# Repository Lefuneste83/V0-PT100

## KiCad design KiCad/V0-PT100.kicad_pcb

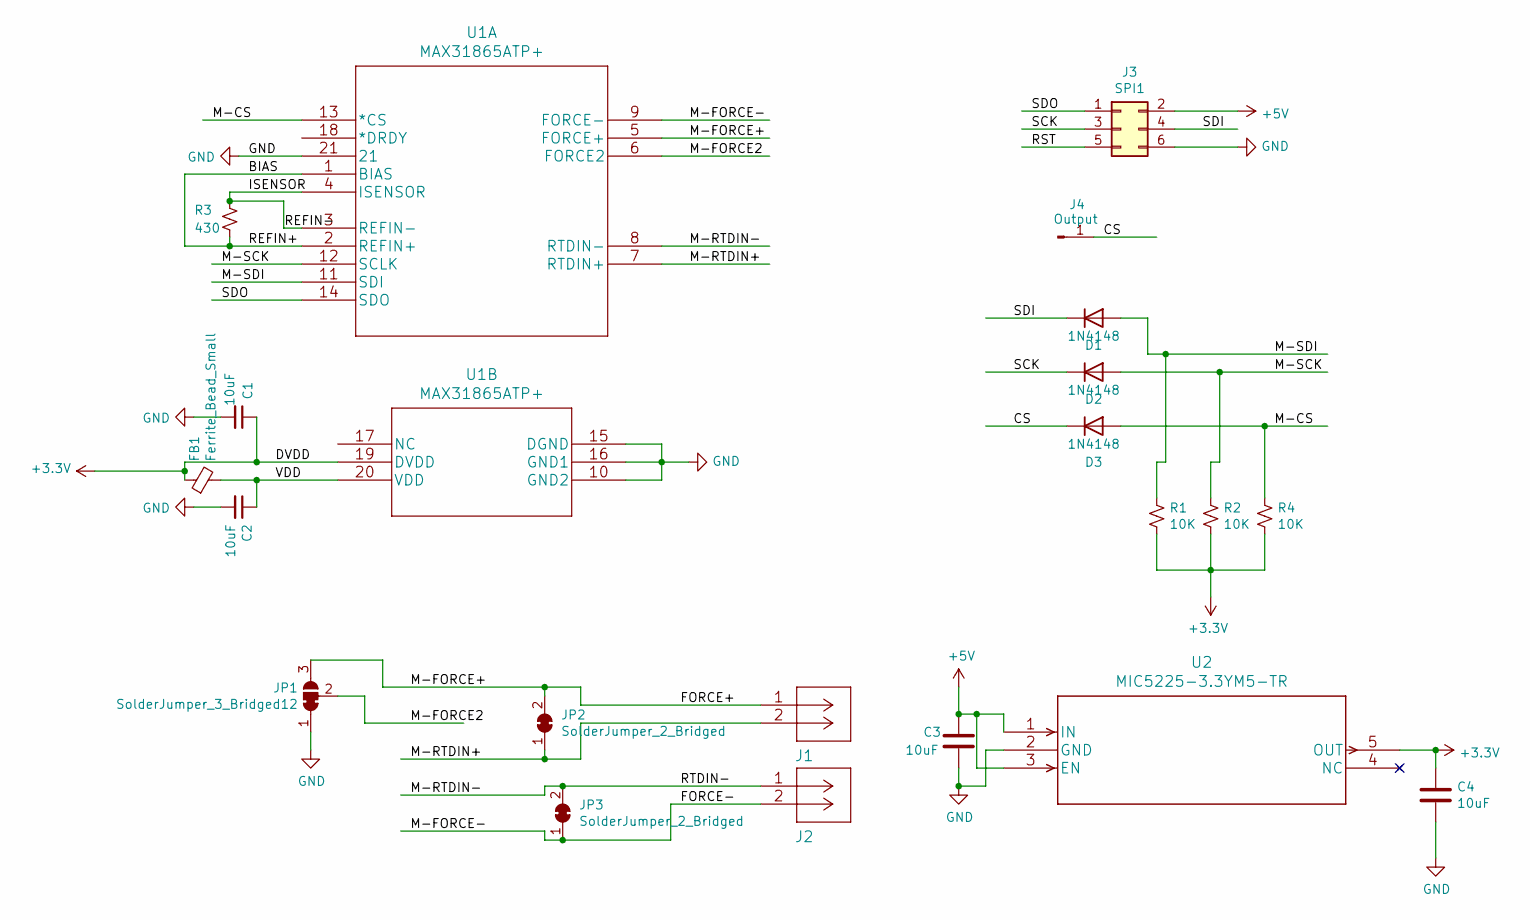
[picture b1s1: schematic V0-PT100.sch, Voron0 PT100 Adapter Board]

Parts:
C1, C2, C3, C4: 10uF; C_0603_1608Metric_Pad1.05x0.95mm_HandSolder
D1, D2, D3: 1N4148; D_SOD-323
FB1: Ferrite_Bead_Small; L_0603_1608Metric_Pad1.05x0.95mm_HandSolder
J1: T1; 1984617
J2: T2; 1984617
J3: SPI1; PinSocket_2x03_P2.54mm_Vertical
J4: Output; PinHeader_1x01_P2.54mm_Horizontal
JP1: SolderJumper_3_Bridged12; SolderJumper-3_P1.3mm_Bridged12_RoundedPad1.0x1.5mm
JP2, JP3: SolderJumper_2_Bridged; SolderJumper-2_P1.3mm_Bridged_RoundedPad1.0x1.5mm
R1, R2, R4: 10K; R_0603_1608Metric_Pad1.05x0.95mm_HandSolder
R3: 430; R_0603_1608Metric_Pad1.05x0.95mm_HandSolder
U1: MAX31865ATP+; MAX31865ATP&plus_
U2: MIC5225-3.3YM5-TR

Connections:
+3V3: C1.1, C4.1, FB1.1, R1.2, R2.2, R4.2, U1.19 (DVDD), U2.5 (OUT)
+5V: C3.1, J3.2, U2.1 (IN), U2.3 (EN)
/BIAS: R3.2, U1.1 (BIAS), U1.2 (REFIN+)
/CS: D3.1 (K), J4.1
/FORCE+: J1.1, JP1.3 (B), JP2.2 (B), U1.5 (FORCE+)
/FORCE-: J2.2, JP3.1 (A), U1.9 (FORCE-)
/ISENSOR: R3.1, U1.3 (REFIN-), U1.4 (ISENSOR)
/M-CS: D3.2 (A), R4.1, U1.13 (*CS)
/M-FORCE2: JP1.2 (C), U1.6 (FORCE2)
/M-RTDIN+: J1.2, JP2.1 (A), U1.7 (RTDIN+)
/M-RTDIN-: J2.1, JP3.2 (B), U1.8 (RTDIN-)
/M-SCK: D2.2 (A), R2.1, U1.12 (SCLK)
/M-SDI: D1.2 (A), R1.1, U1.11 (SDI)
/RST: J3.5
/SCK: D2.1 (K), J3.3
/SDI: D1.1 (K), J3.4
/SDO: J3.1, U1.14 (SDO)
/VDD: C2.1, FB1.2, U1.20 (VDD)
GND: C1.2, C2.2, C3.2, C4.2, J3.6, JP1.1 (A), U1.10 (GND2), U1.15 (DGND), U1.16 (GND1), U1.21, U2.2 (GND)

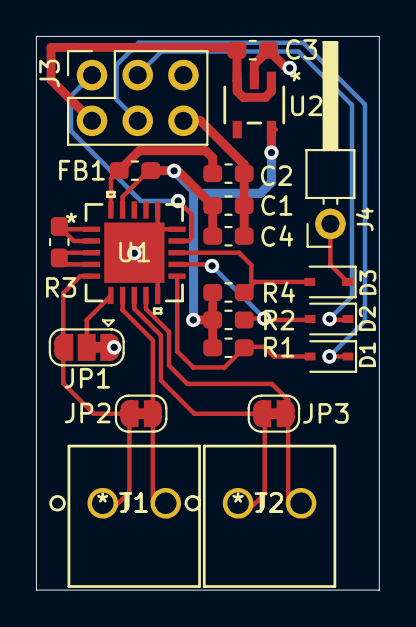
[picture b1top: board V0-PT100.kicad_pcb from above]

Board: 2 copper layers, 19.0 x 30.8 mm, 21 parts (0 on the bottom side), 18 nets.

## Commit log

2020-07-17 Create LICENSE
2020-07-17 Inital Project Start
2020-07-17 Inital PT100 Adapter schematic
2020-07-18 Schematic Updates. Next Up PCB layout
2020-07-18 Swap out some component
2020-07-18 Update PCB parts
2020-07-19 Inital PCB layout complete
2020-09-08 Updated PCB layout
    Changed the routing to a simplified one, thickened the power lines, poured a ground plane, resized the PCB

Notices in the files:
parts and their libraries:
Copyright 2016 Accelerated Designs. All rights reserved.
